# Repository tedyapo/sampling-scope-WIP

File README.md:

# sampling-scope-WIP
Work towards an open-source multi-GHz sampling oscilloscope design

Board designs are in Eagle. They are 4-layer, so require a subscription license to edit (I believe).

NB: as titled, this project is very much a work-in-progress. Completed designs will be published elsewhere.

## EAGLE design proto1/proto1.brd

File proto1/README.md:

# proto 1

This version does not include internal timebase calibration.

Initial testing has shown that it functions as a sampling oscilloscope with a bandwidth of approximately 6.7 GHz.

There is an error in this design: I swapped op-amps at the last minute, and accidentally reversed the inputs in the scheamtic. The board needs rework to correct this.

This version is abandoned, as it was never entended as a final product, just as a testbed for an evolving design.

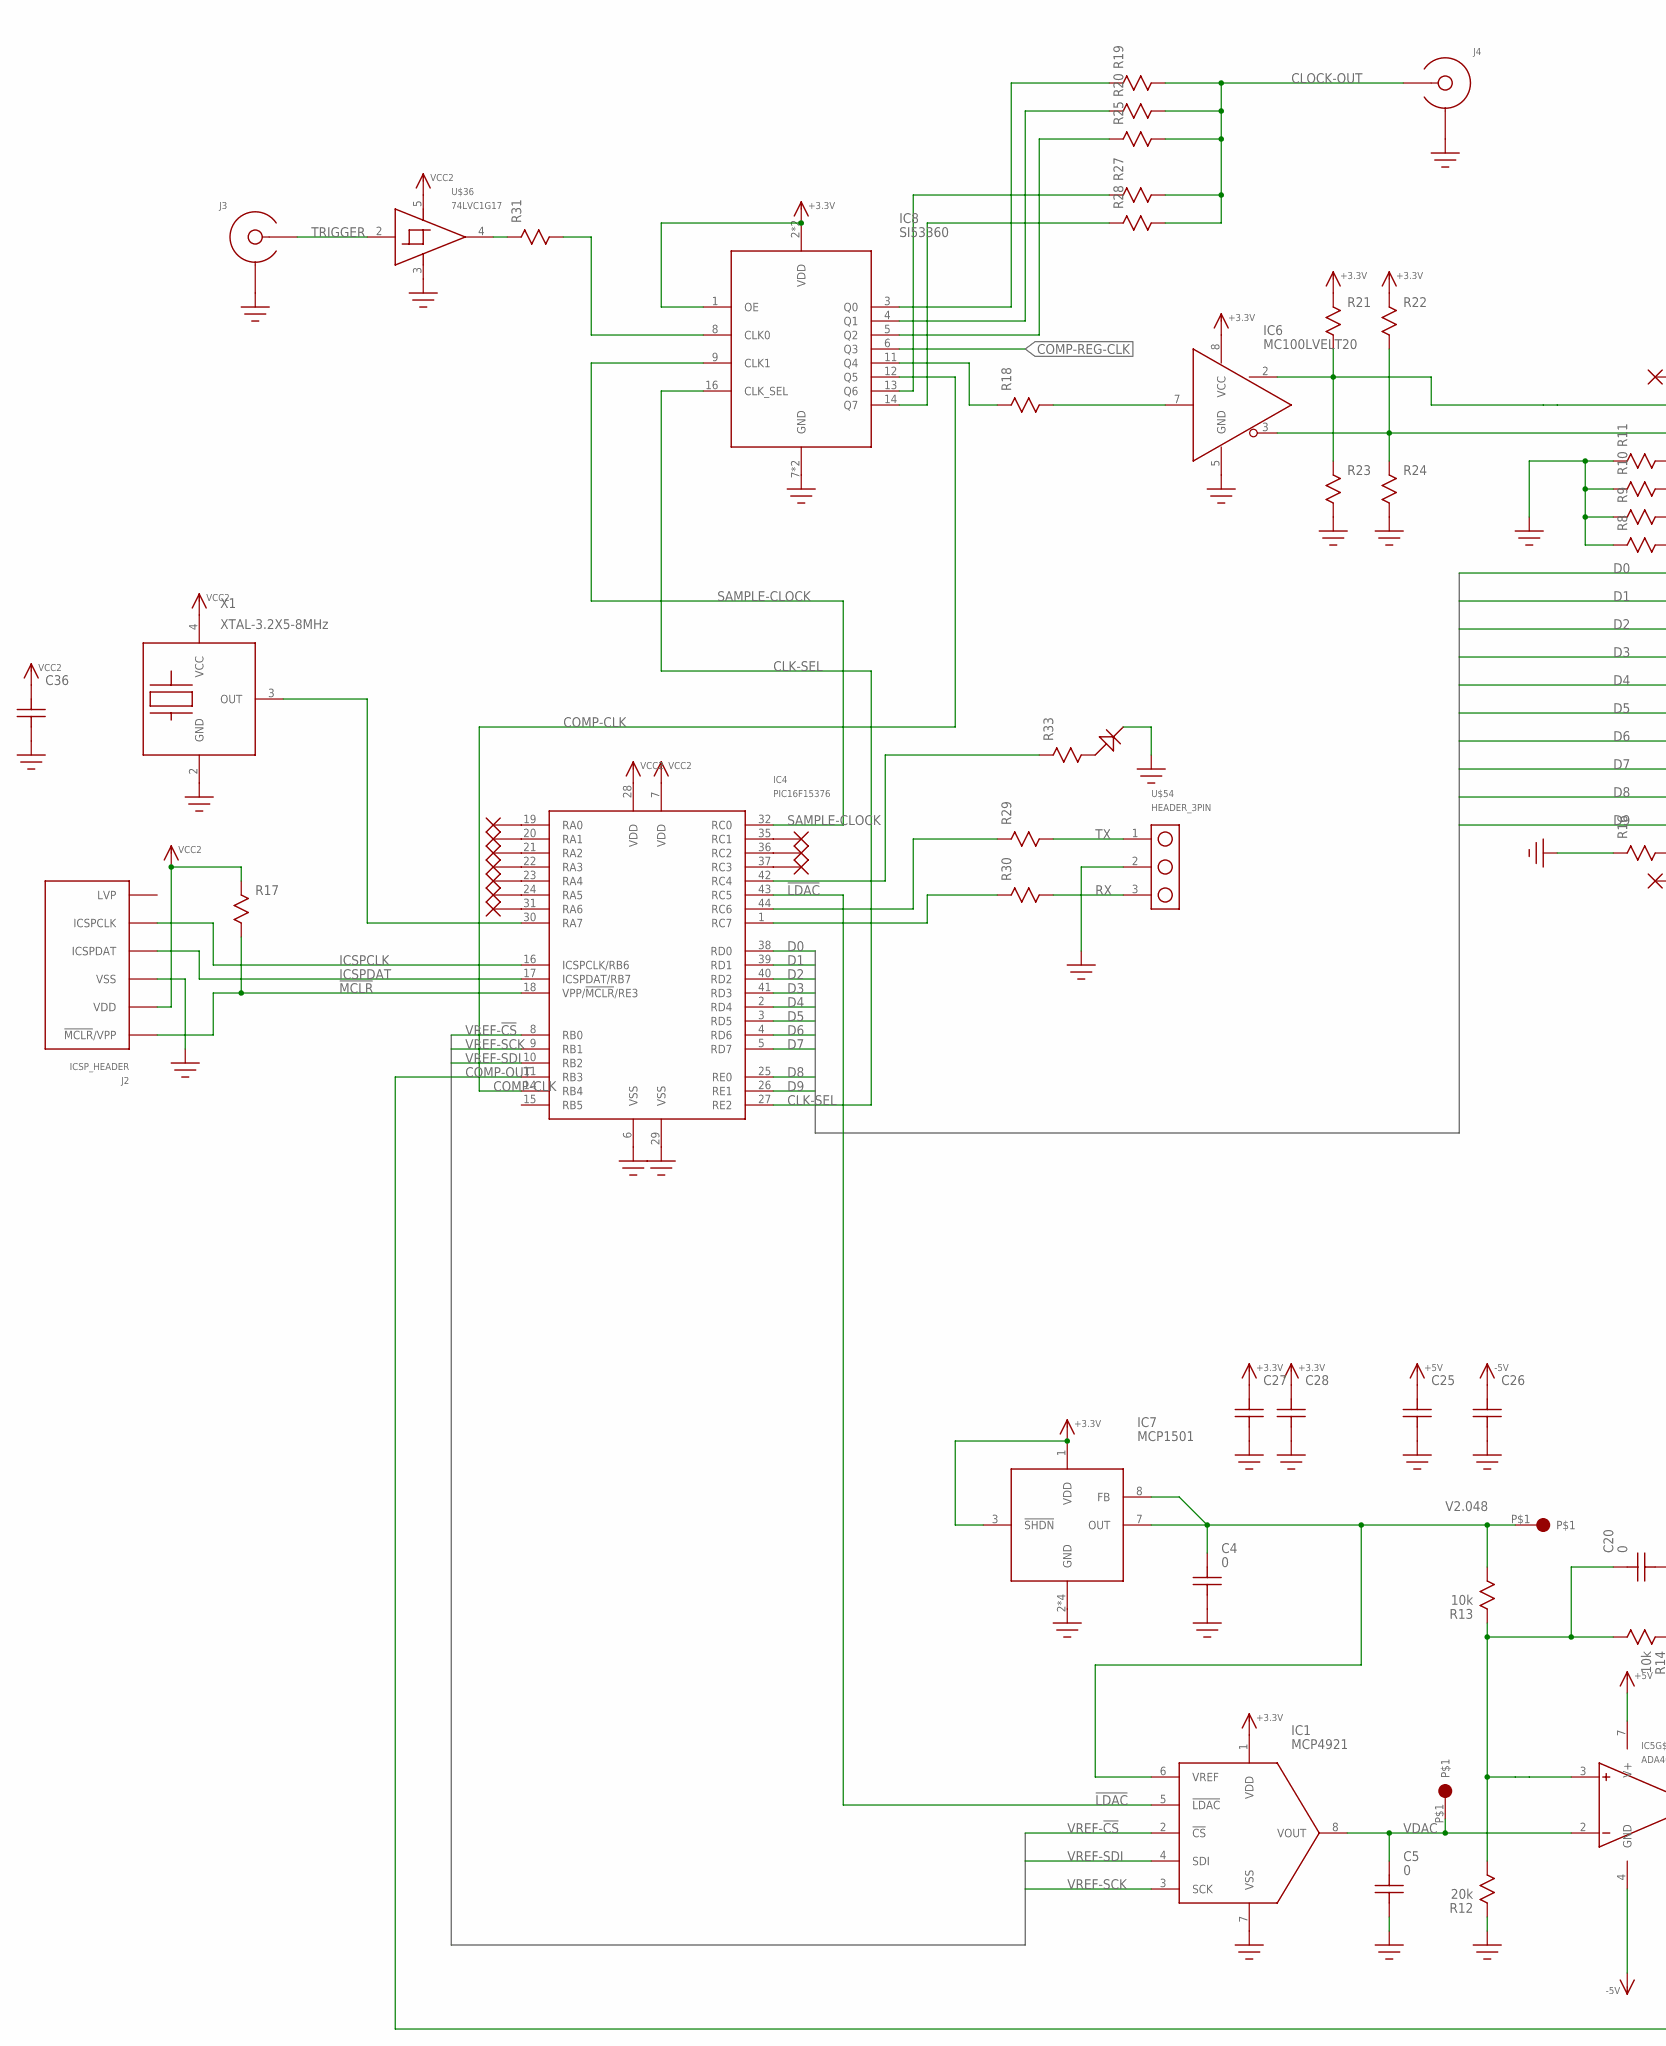
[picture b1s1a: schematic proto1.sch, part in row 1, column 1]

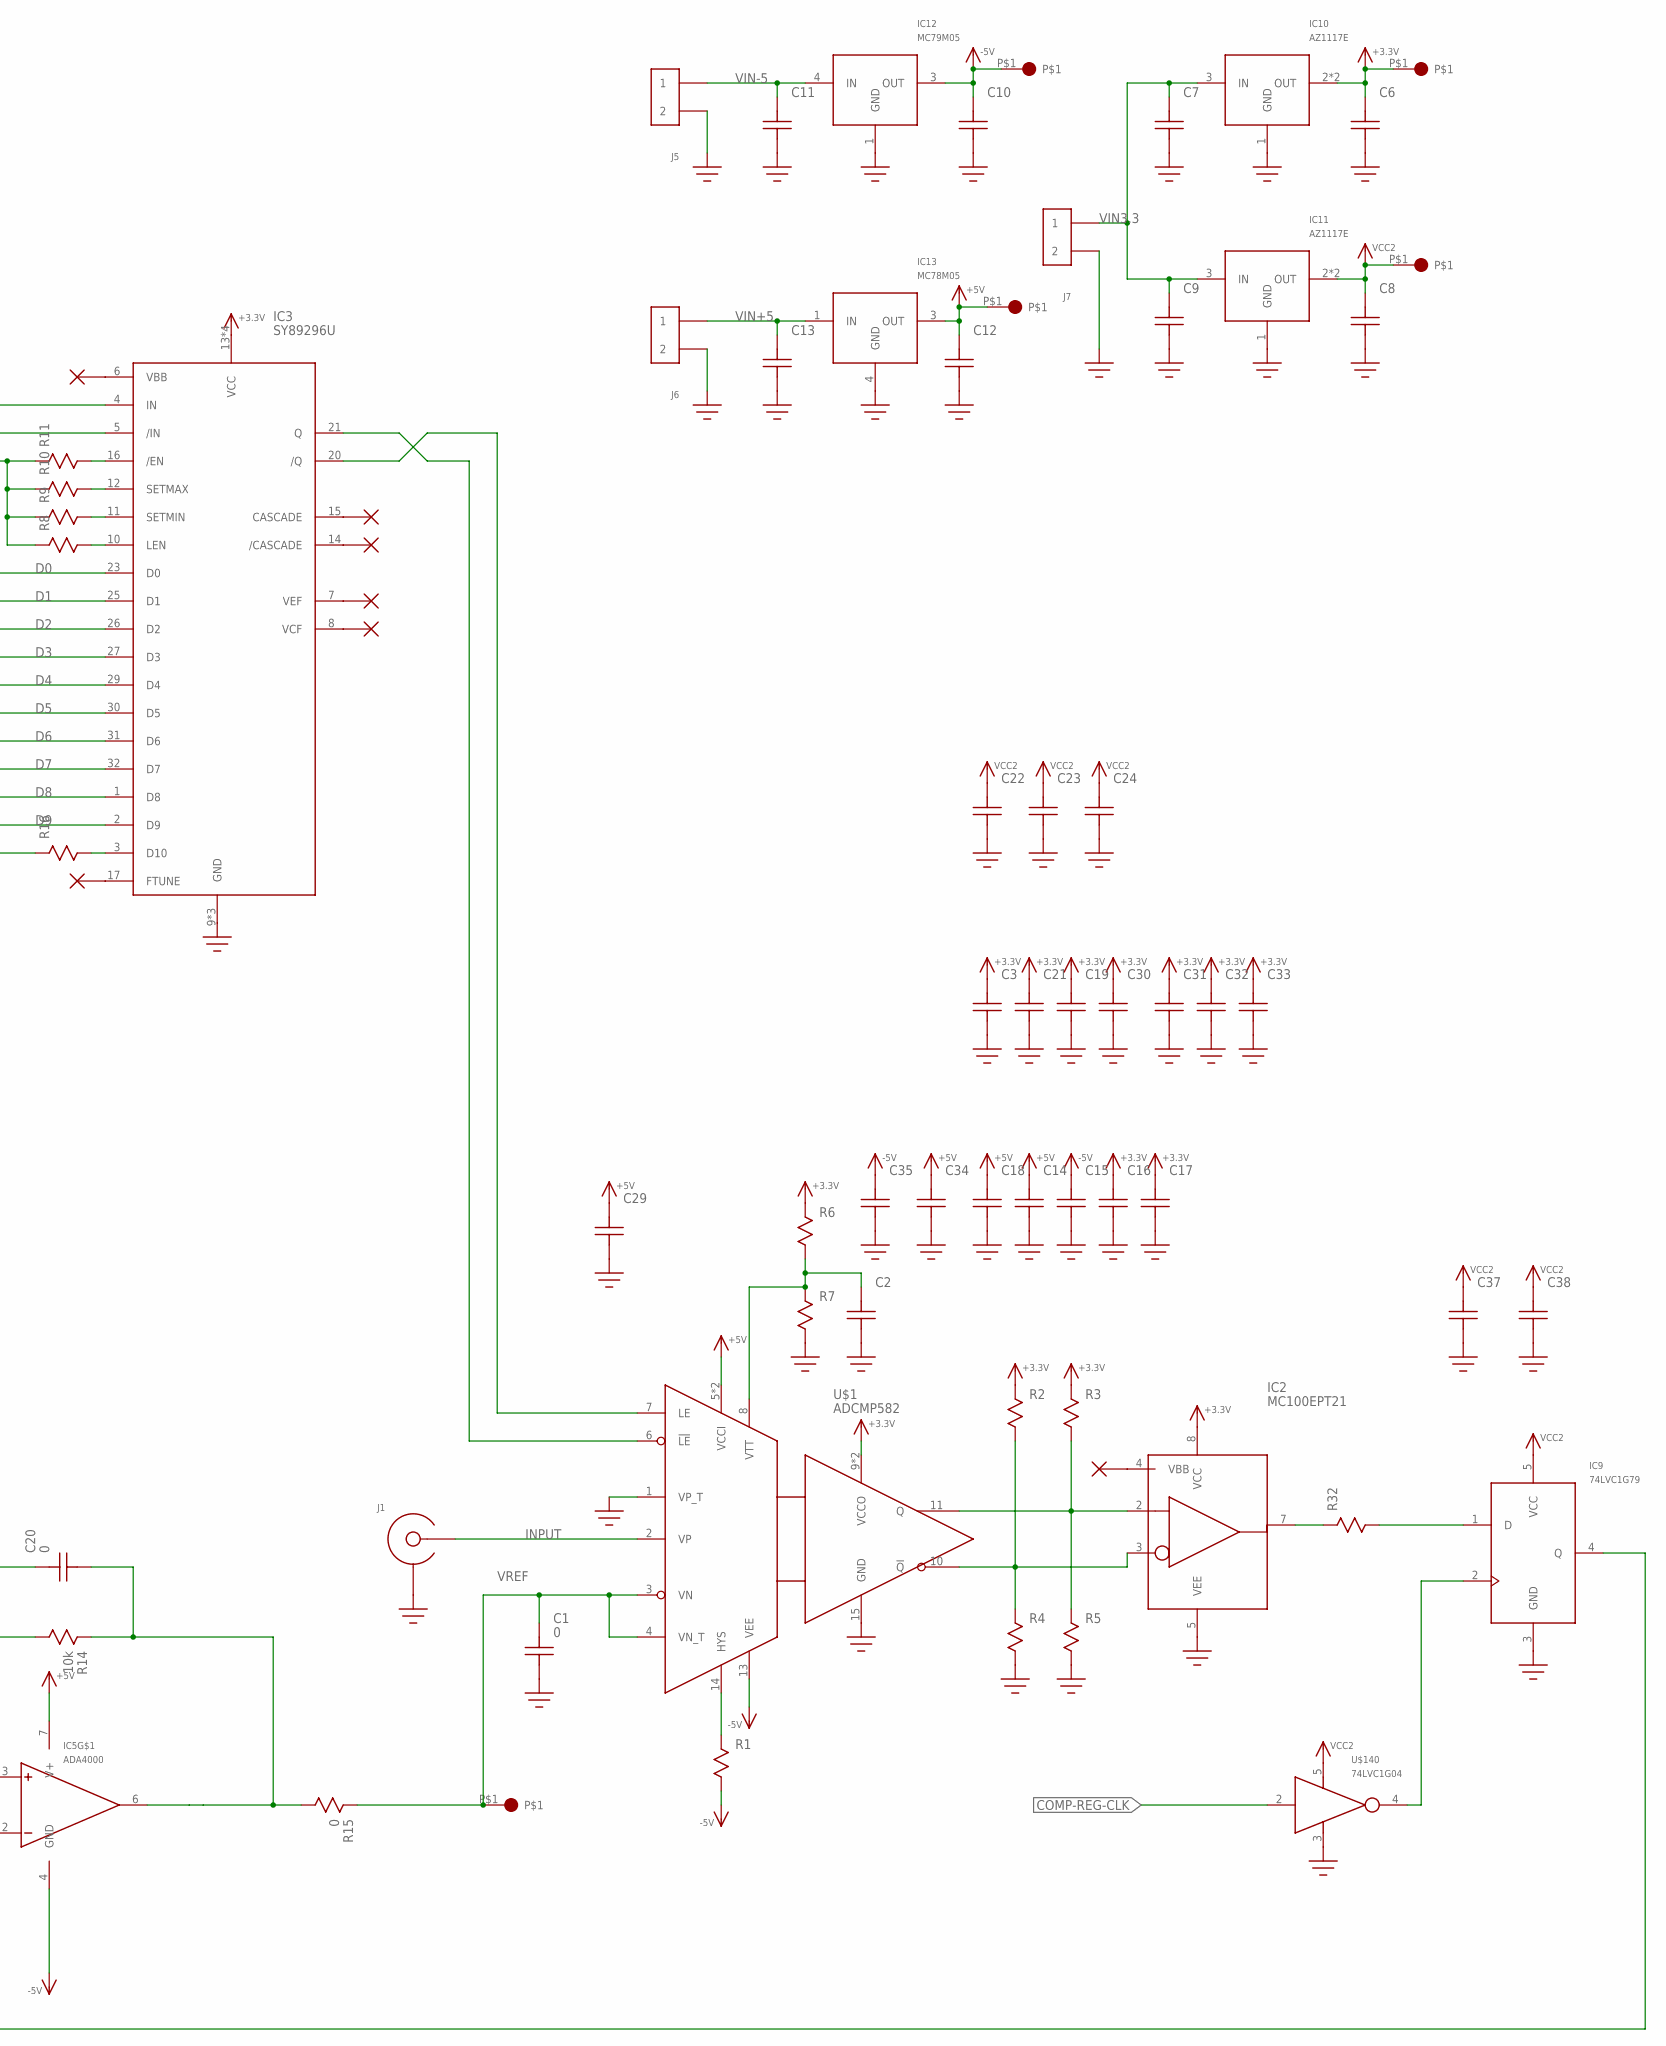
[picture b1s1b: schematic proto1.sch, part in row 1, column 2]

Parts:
C1, C4, C5, C20: 0; C0603
C2, C14, C15, C16, C17, C18: C0402_NO_THERMALS
C3, C19, C21, C22, C23, C24, C25, C26, C27, C28, C30, C31, C32, C33, C34, C35, C36, C37, C38: C0603
C6, C7, C8, C9, C10, C11, C12, C13, C29: C1206; 1206
IC1: MCP4921; SOIC8
IC2: MC100EPT21; SOIC8
IC3: SY89296U; TQFP32_7X7
IC4: PIC16F15376; TQFP44
IC5: ADA4000; SOIC8
IC6: MC100LVELT20; SOIC8
IC7: MCP1501; SOIC8
IC8: SI53360; TSSOP16
IC9: 74LVC1G79; SOT23-5
IC10, IC11: AZ1117E; SOT-223
IC12: MC79M05; DPAK
IC13: MC78M05; DPAK
J1, J3, J4: SMA-EDGE-LAUNCH4L-4020-TAPER-FIXED; SMA_EDGE_LAUNCH_4L_4020_TAPER_FIXED
J2: ICSP_HEADER; HEADER_6PIN
J5, J6, J7: HEADER_2PINSCREW-TERM; FCI_20020316_SCREW_TERM_2P
P1, P2, P3, P4, P5, P6, P7: ICSP_PAD
R1, R2, R3, R4, R5, R6, R7, R16, R17, R18, R21, R22, R23, R24, R29, R30, R31, R32, R33: R0603
R8, R9, R10, R11, R19, R20, R25, R27, R28: R0402; 0402
R12: 20k; R0603
R13, R14: 10k; R0603
R15: 0; R0603
U$1: ADCMP582; TQFN16-EP
U$36: 74LVC1G17; SOT23-5
U$54: HEADER_3PIN
U$88: LED_0603
U$140: 74LVC1G04; SOT23-5
X1: XTAL-3.2X5-8MHz; XTAL_3.2X5

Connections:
!LDAC!: IC1.5 (!LDAC!), IC4.43 (RC5)
!MCLR!: IC4.18 (VPP/!MCLR!/RE3), J2.1 (!MCLR!/VPP), R17.P$2
+3.3V: C3.P$2, C6.P$2, C16.2, C17.2, C19.P$2, C21.P$2, C27.P$2, C28.P$2, C30.P$2, C31.P$2, C32.P$2, C33.P$2, IC1.1 (VDD), IC2.8 (VCC), IC3.13 (VCC), IC3.18 (VCC), IC3.19 (VCC), IC3.22 (VCC), IC6.8 (VCC), IC7.1 (VDD), IC7.3 (!SHDN!), IC8.1 (OE), IC8.2 (VDD), IC8.15 (VDD), IC10.2 (OUT), IC10.4 (OUT), P5.P$1, R2.P$1, R3.P$1, R6.P$1, R21.P$1, R22.P$1, U$1.9 (VCCO), U$1.12 (VCCO)
+5V: C12.P$2, C14.2, C18.2, C25.P$2, C29.P$2, C34.P$2, IC5.7 (V+), IC13.3 (OUT), P4.P$1, U$1.5 (VCCI), U$1.16 (VCCI)
-5V: C10.P$2, C15.2, C26.P$2, C35.P$2, IC5.4 (GND), IC12.3 (OUT), P3.P$1, R1.P$2, U$1.13 (VEE)
CLK-SEL: IC4.27 (RE2), IC8.16 (CLK_SEL)
CLOCK-OUT: J4.CENTER@1 (CENTER), J4.P$3 (CENTER), R19.2, R20.2, R25.2, R27.2, R28.2
COMP-CLK: IC4.14 (RB4), IC8.12 (Q5)
COMP-OUT: IC4.11 (RB3), IC9.4 (Q)
COMP-REG-CLK: IC8.6 (Q3), U$140.2 (IN)
D0: IC3.23 (D0), IC4.38 (RD0)
D1: IC3.25 (D1), IC4.39 (RD1)
D2: IC3.26 (D2), IC4.40 (RD2)
D3: IC3.27 (D3), IC4.41 (RD3)
D4: IC3.29 (D4), IC4.2 (RD4)
D5: IC3.30 (D5), IC4.3 (RD5)
D6: IC3.31 (D6), IC4.4 (RD6)
D7: IC3.32 (D7), IC4.5 (RD7)
D8: IC3.1 (D8), IC4.25 (RE0)
D9: IC3.2 (D9), IC4.26 (RE1)
GND: C1.P$1, C2.1, C3.P$1, C4.P$1, C5.P$1, C6.P$1, C7.P$1, C8.P$1, C9.P$1, C10.P$1, C11.P$1, C12.P$1, C13.P$1, C14.1, C15.1, C16.1, C17.1, C18.1, C19.P$1, C21.P$1, C22.P$1, C23.P$1, C24.P$1, C25.P$1, C26.P$1, C27.P$1, C28.P$1, C29.P$1, C30.P$1, C31.P$1, C32.P$1, C33.P$1, C34.P$1, C35.P$1, C36.P$1, C37.P$1, C38.P$1, IC1.7 (VSS), IC2.5 (VEE), IC3.9 (GND), IC3.24 (GND), IC3.28 (GND), IC4.6 (VSS), IC4.29 (VSS), IC6.5 (GND), IC7.2 (GND), IC7.4 (GND), IC7.5 (GND), IC7.6 (GND), IC8.7 (GND), IC8.10 (GND), IC9.3 (GND), IC10.1 (GND), IC11.1 (GND), IC12.1 (GND), IC13.4 (GND), J1.BOTTOM_GND (SHIELD), J1.GND@1 (SHIELD), J1.GND@2 (SHIELD), J1.GND@3 (SHIELD), J1.GND@4 (SHIELD), J1.GND@5 (SHIELD), J1.GND@6 (SHIELD), J1.GND@7 (SHIELD), J1.GND@8 (SHIELD), J1.GND@14 (SHIELD), J1.GND@15 (SHIELD), J1.GND@16 (SHIELD), J1.GND@17 (SHIELD), J1.GND_PAD1 (SHIELD), J1.GND_PAD2 (SHIELD), J1.P$1 (SHIELD), J1.P$2 (SHIELD), J2.3 (VSS), J3.BOTTOM_GND (SHIELD), J3.GND@1 (SHIELD), J3.GND@2 (SHIELD), J3.GND@3 (SHIELD), J3.GND@4 (SHIELD), J3.GND@5 (SHIELD), J3.GND@6 (SHIELD), J3.GND@7 (SHIELD), J3.GND@8 (SHIELD), J3.GND@14 (SHIELD), J3.GND@15 (SHIELD), J3.GND@16 (SHIELD), J3.GND@17 (SHIELD), J3.GND_PAD1 (SHIELD), J3.GND_PAD2 (SHIELD), J3.P$1 (SHIELD), J3.P$2 (SHIELD), J4.BOTTOM_GND (SHIELD), J4.GND@1 (SHIELD), J4.GND@2 (SHIELD), J4.GND@3 (SHIELD), J4.GND@4 (SHIELD), J4.GND@5 (SHIELD), J4.GND@6 (SHIELD), J4.GND@7 (SHIELD), J4.GND@8 (SHIELD), J4.GND@14 (SHIELD), J4.GND@15 (SHIELD), J4.GND@16 (SHIELD), J4.GND@17 (SHIELD), J4.GND_PAD1 (SHIELD), J4.GND_PAD2 (SHIELD), J4.P$1 (SHIELD), J4.P$2 (SHIELD), J5.P$2 (2), J6.P$2 (2), J7.P$2 (2), R4.P$2, R5.P$2, R7.P$2, R8.1, R9.1, R10.1, R11.1, R12.P$1, R16.P$1, R23.P$2, R24.P$2, U$1.1 (VP_T), U$1.15 (GND), U$36.3 (GND), U$54.2, U$88.C, U$140.3 (GND), X1.2 (GND)
ICSPCLK: IC4.16 (ICSPCLK/RB6), J2.5 (ICSPCLK)
ICSPDAT: IC4.17 (ICSPDAT/RB7), J2.4 (ICSPDAT)
INPUT: J1.CENTER@1 (CENTER), J1.P$3 (CENTER), U$1.2 (VP)
LE_N: IC3.21 (Q), U$1.6 (!LE!)
LE_P1: IC3.20 (/Q), U$1.7 (LE)
unnamed: R31.P$1, U$36.4 (OUT)
unnamed: R1.P$1, U$1.14 (HYS)
unnamed: IC2.2 (D), R3.P$2, R5.P$1, U$1.11 (Q)
unnamed: IC2.3 (!D!), R2.P$2, R4.P$1, U$1.10 (!Q!)
unnamed: C2.2, R6.P$2, R7.P$1, U$1.8 (VTT)
unnamed: IC3.16 (/EN), R11.2
unnamed: IC3.12 (SETMAX), R10.2
unnamed: IC3.11 (SETMIN), R9.2
unnamed: IC3.10 (LEN), R8.2
unnamed: IC3.4 (IN), IC6.2 (Q), R21.P$2, R23.P$1
unnamed: IC2.7 (Q), R32.P$1
unnamed: IC8.11 (Q4), R18.P$1
unnamed: IC9.2 (CLK), U$140.4 (OUT)
unnamed: C20.P$2, IC5.3 (+), R12.P$2, R13.P$1, R14.P$2
unnamed: C20.P$1, IC5.6 (OUT), R14.P$1, R15.P$2
unnamed: IC3.5 (/IN), IC6.3 (!Q!), R22.P$2, R24.P$1
unnamed: IC8.8 (CLK0), R31.P$2
unnamed: IC4.30 (RA7), X1.3 (OUT)
unnamed: IC4.42 (RC4), R33.P$1
unnamed: R33.P$2, U$88.A
unnamed: IC9.1 (D), R32.P$2
unnamed: IC3.3 (D10), R16.P$2
unnamed: IC6.7 (D), R18.P$2
unnamed: IC8.14 (Q7), R28.1
unnamed: IC8.13 (Q6), R27.1
unnamed: IC8.5 (Q2), R25.1
unnamed: IC8.4 (Q1), R20.1
unnamed: IC8.3 (Q0), R19.1
unnamed: IC4.44 (RC6), R29.P$1
unnamed: IC4.1 (RC7), R30.P$1
RX: R30.P$2, U$54.3
SAMPLE-CLOCK: IC4.32 (RC0), IC8.9 (CLK1)
TRIGGER: J3.CENTER@1 (CENTER), J3.P$3 (CENTER), U$36.2 (IN)
TX: R29.P$2, U$54.1
V2.048: C4.P$2, IC1.6 (VREF), IC7.7 (OUT), IC7.8 (FB), P7.P$1, R13.P$2
VCC2: C8.P$2, C22.P$2, C23.P$2, C24.P$2, C36.P$2, C37.P$2, C38.P$2, IC4.7 (VDD), IC4.28 (VDD), IC9.5 (VCC), IC11.2 (OUT), IC11.4 (OUT), J2.2 (VDD), P6.P$1, R17.P$1, U$36.5 (VCC), U$140.5 (VCC), X1.4 (VCC)
VDAC: C5.P$2, IC1.8 (VOUT), IC5.2 (-), P2.P$1
VIN3.3: C7.P$2, C9.P$2, IC10.3 (IN), IC11.3 (IN), J7.P$1 (1)
VIN+5: C13.P$2, IC13.1 (IN), J6.P$1 (1)
VIN-5: C11.P$2, IC12.4 (IN), J5.P$1 (1)
VREF: C1.P$2, P1.P$1, R15.P$1, U$1.3 (VN), U$1.4 (VN_T)
VREF-!CS!: IC1.2 (!CS!), IC4.8 (RB0)
VREF-SCK: IC1.3 (SCK), IC4.9 (RB1)
VREF-SDI: IC1.4 (SDI), IC4.10 (RB2)

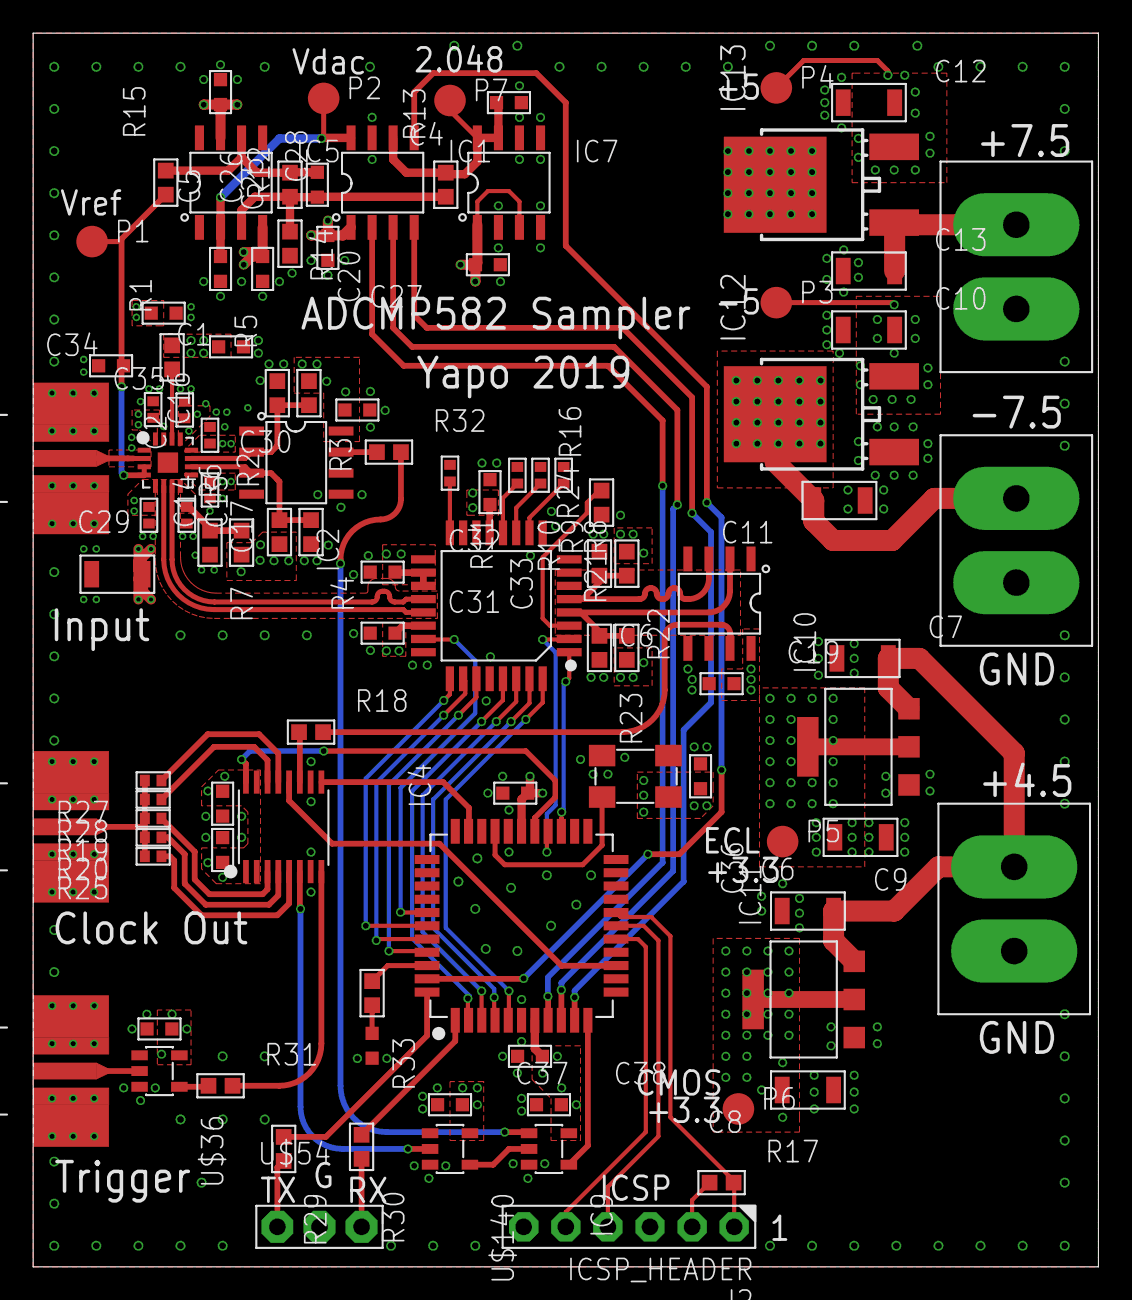
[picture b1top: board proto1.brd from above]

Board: 4 copper layers, 64.3 x 74.4 mm, 103 parts (0 on the bottom side), 70 nets.

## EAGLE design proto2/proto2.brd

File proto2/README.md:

# proto2

This version incorporates the timebase calibration loop.

It has not been fully tested yet.

This version will be abandoned, as it was never entended as a final product, just as a testbed for an evolving design.

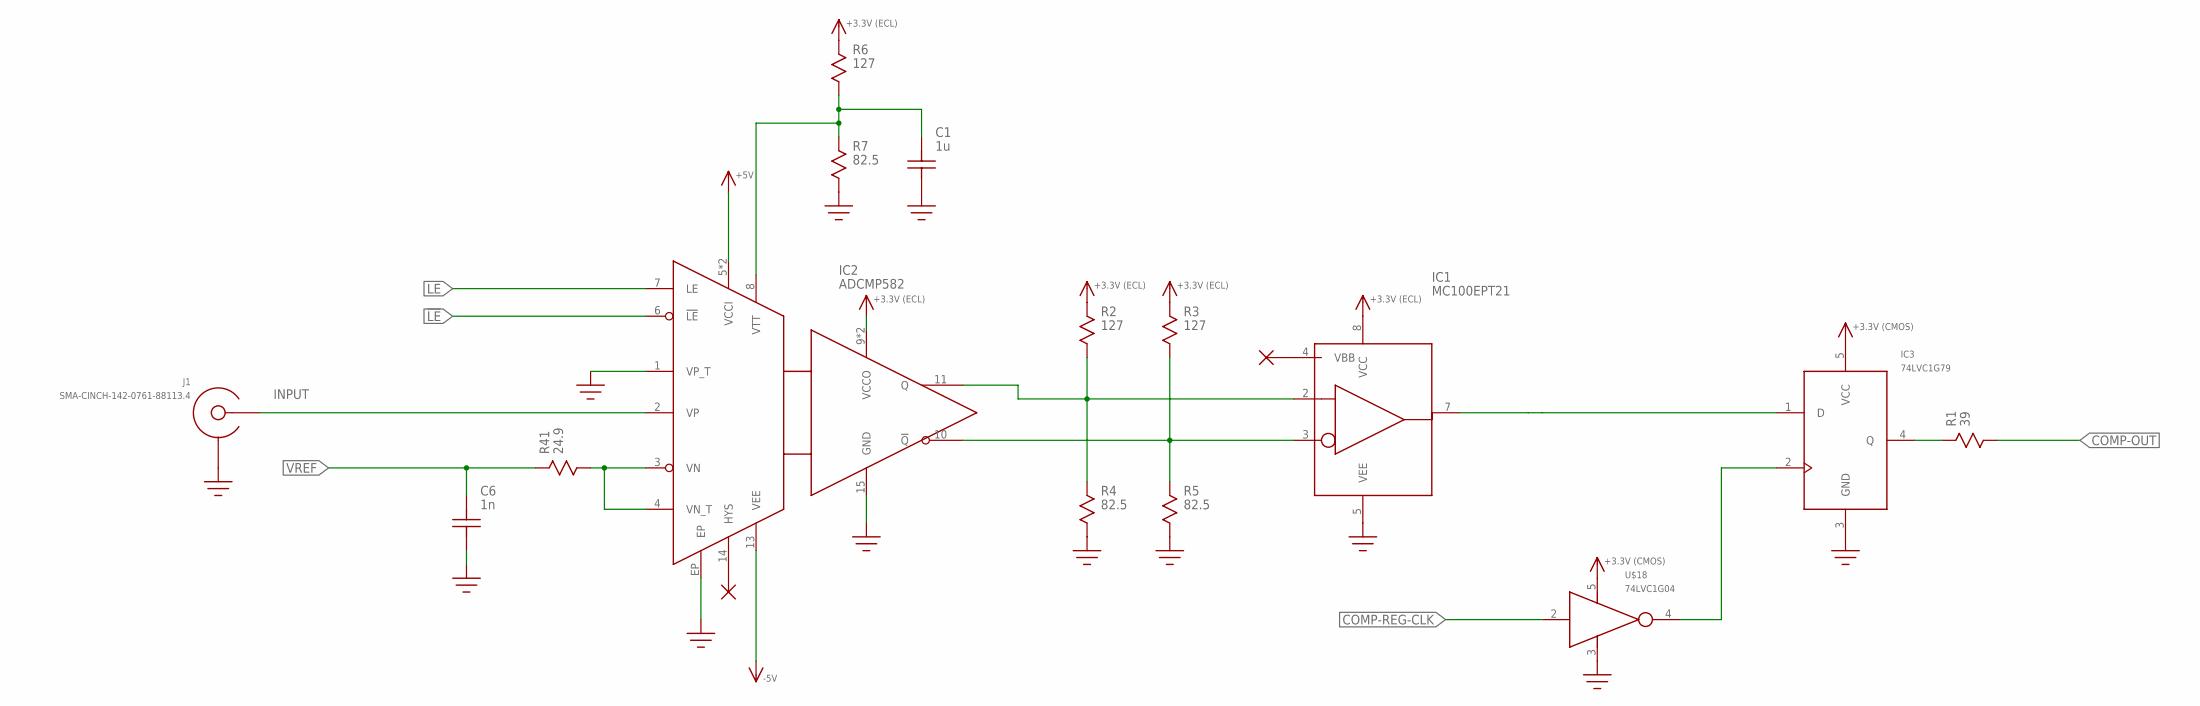
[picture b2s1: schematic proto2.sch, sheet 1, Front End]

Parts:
C1: 1u; C0402
C6: 1n; C0402
IC1: MC100EPT21; SOIC8
IC2: ADCMP582; TQFN16-EP
IC3: 74LVC1G79; SOT23-5
J1: SMA-CINCH-142-0761-88113.4; SMA-CINCH-142-0761-881-13.4
R1: 39; R0603
R2, R3, R6: 127; R0603
R4, R5, R7: 82.5; R0603
R41: 24.9; 0402
U$18: 74LVC1G04; SOT23-5

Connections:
!LE!: IC2.6 (!LE!); also elsewhere on the board
+5V: IC2.5 (VCCI), IC2.16 (VCCI); also elsewhere on the board
-5V: IC2.13 (VEE); also elsewhere on the board
COMP-OUT: R1.P$2; also elsewhere on the board
COMP-REG-CLK: U$18.2 (IN); also elsewhere on the board
GND: C1.1, C6.1, IC1.5 (VEE), IC2.1 (VP_T), IC2.15 (GND), IC2.EP, IC3.3 (GND), J1.GND@1 (SHIELD), J1.GND@2 (SHIELD), J1.GND@3 (SHIELD), J1.HOLE@1 (SHIELD), J1.HOLE@2 (SHIELD), J1.HOLE@3 (SHIELD), J1.HOLE@4 (SHIELD), J1.VIA@1 (SHIELD), J1.VIA@2 (SHIELD), J1.VIA@3 (SHIELD), J1.VIA@4 (SHIELD), J1.VIA@5 (SHIELD), J1.VIA@6 (SHIELD), R4.P$2, R5.P$2, R7.P$2, U$18.3 (GND); also elsewhere on the board
INPUT: IC2.2 (VP), J1.CENTER
LE: IC2.7 (LE); also elsewhere on the board
unnamed: C1.2, IC2.8 (VTT), R6.P$2, R7.P$1
unnamed: IC1.3 (!D!), IC2.10 (!Q!), R3.P$2, R5.P$1
unnamed: IC1.2 (D), IC2.11 (Q), R2.P$2, R4.P$1
unnamed: IC1.7 (Q), IC3.1 (D)
unnamed: IC3.4 (Q), R1.P$1
unnamed: IC3.2 (CLK), U$18.4 (OUT)
unnamed: IC2.3 (VN), IC2.4 (VN_T), R41.2
VCC1: IC1.8 (VCC), IC2.9 (VCCO), IC2.12 (VCCO), R2.P$1, R3.P$1, R6.P$1; also elsewhere on the board
VCC2: IC3.5 (VCC), U$18.5 (VCC); also elsewhere on the board
VREF: C6.2, R41.1; also elsewhere on the board

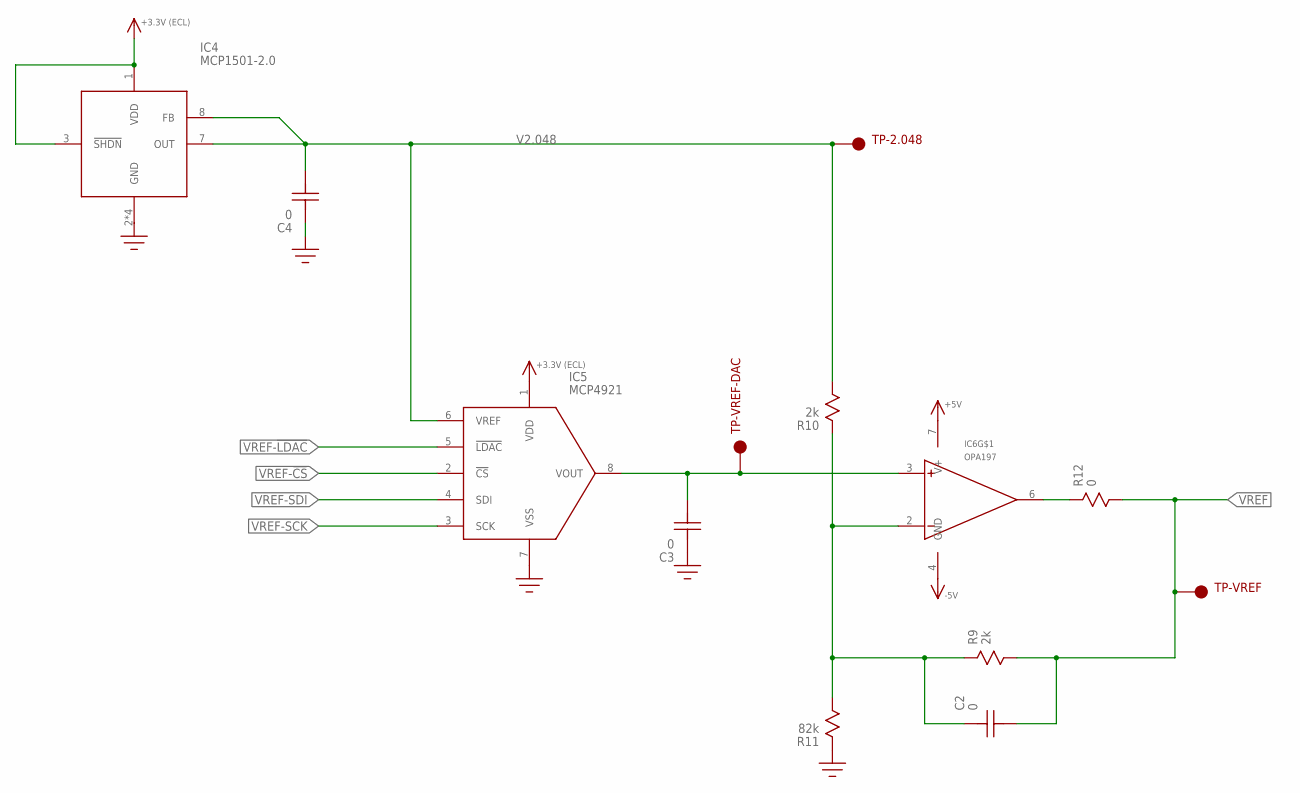
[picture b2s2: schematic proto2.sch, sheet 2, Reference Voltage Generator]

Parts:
C2, C3, C4: 0; C0603
IC4: MCP1501-2.0; SOIC8
IC5: MCP4921; SOIC8
IC6: OPA197; SOIC8
R9, R10: 2k; R0603
R11: 82k; R0603
R12: 0; R0603
TP-2.048: ICSP_PAD
TP-VREF: ICSP_PAD
TP-VREF-DAC: ICSP_PAD

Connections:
+5V: IC6.7 (V+); also elsewhere on the board
-5V: IC6.4 (GND); also elsewhere on the board
GND: C3.P$2, C4.P$2, IC4.2 (GND), IC4.4 (GND), IC4.5 (GND), IC4.6 (GND), IC5.7 (VSS), R11.P$1; also elsewhere on the board
unnamed: C2.P$2, IC6.2 (-), R9.P$1, R10.P$1, R11.P$2
unnamed: IC6.6 (OUT), R12.P$1
unnamed: C3.P$1, IC5.8 (VOUT), IC6.3 (+), TP-VREF-DAC.P$1
V2.048: C4.P$1, IC4.7 (OUT), IC4.8 (FB), IC5.6 (VREF), R10.P$2, TP-2.048.P$1
VCC1: IC4.1 (VDD), IC4.3 (!SHDN!), IC5.1 (VDD); also elsewhere on the board
VREF: C2.P$1, R9.P$2, R12.P$2, TP-VREF.P$1; also elsewhere on the board
VREF-!CS!: IC5.2 (!CS!); also elsewhere on the board
VREF-!LDAC!: IC5.5 (!LDAC!); also elsewhere on the board
VREF-SCK: IC5.3 (SCK); also elsewhere on the board
VREF-SDI: IC5.4 (SDI); also elsewhere on the board

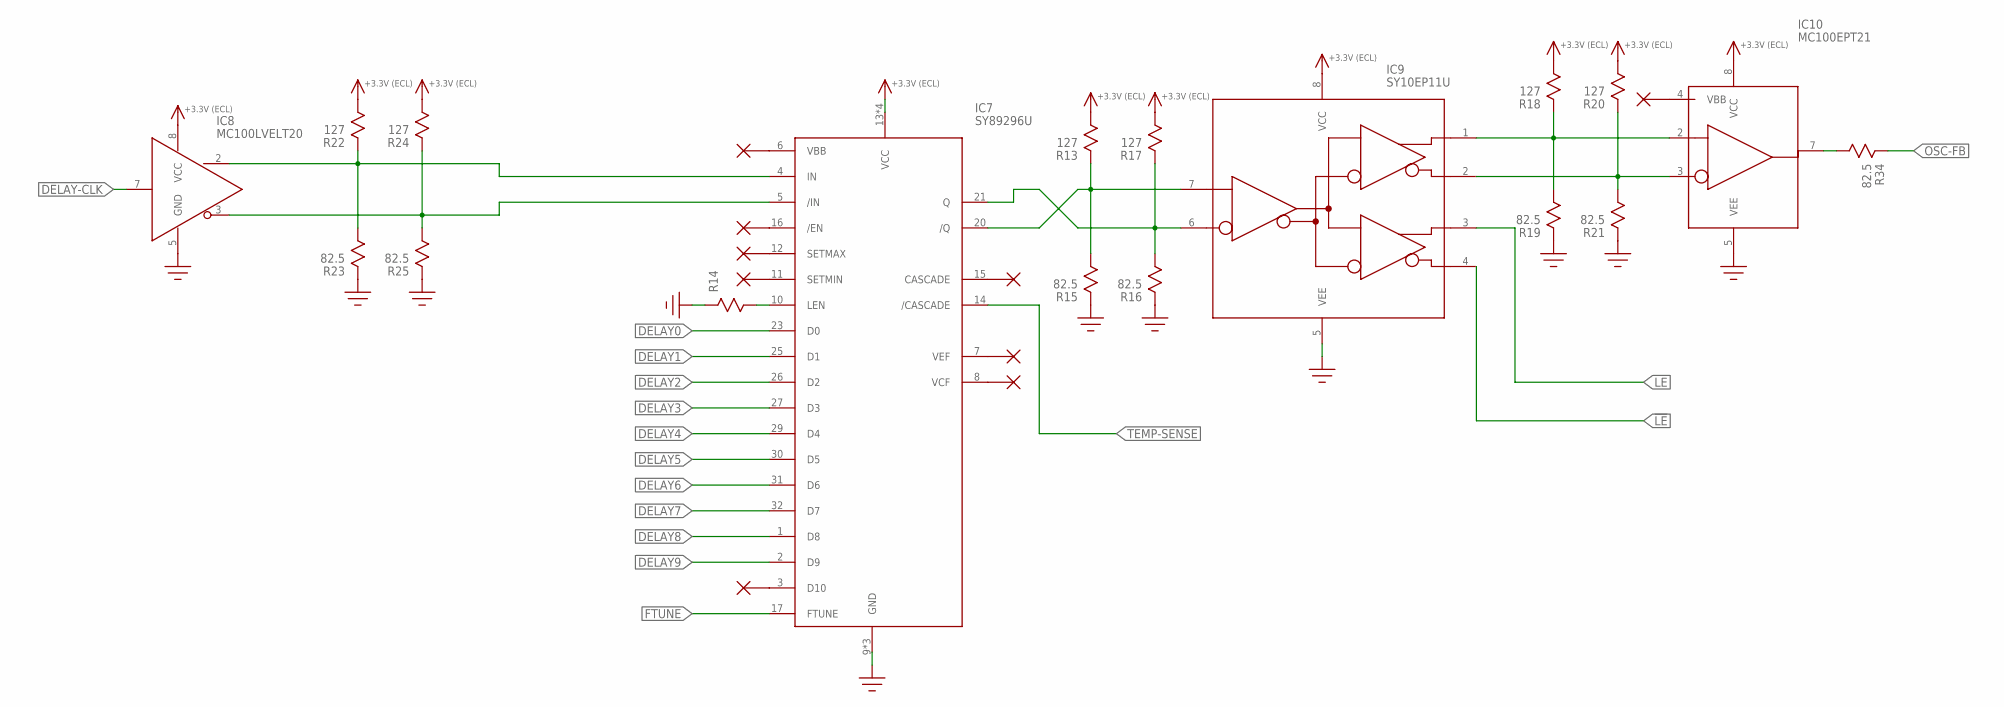
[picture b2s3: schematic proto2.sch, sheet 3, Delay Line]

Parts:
IC7: SY89296U; TQFP32_7X7
IC8: MC100LVELT20; SOIC8
IC9: SY10EP11U; SOIC8
IC10: MC100EPT21; SOIC8
R13, R17, R18, R20, R22, R24: 127; R0603
R14: R0603
R15, R16, R19, R21, R23, R25, R34: 82.5; R0603

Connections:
!LE!: IC9.4 (!Q1!); also elsewhere on the board
DELAY0: IC7.23 (D0); also elsewhere on the board
DELAY1: IC7.25 (D1); also elsewhere on the board
DELAY2: IC7.26 (D2); also elsewhere on the board
DELAY3: IC7.27 (D3); also elsewhere on the board
DELAY4: IC7.29 (D4); also elsewhere on the board
DELAY5: IC7.30 (D5); also elsewhere on the board
DELAY6: IC7.31 (D6); also elsewhere on the board
DELAY7: IC7.32 (D7); also elsewhere on the board
DELAY8: IC7.1 (D8); also elsewhere on the board
DELAY9: IC7.2 (D9); also elsewhere on the board
DELAY-!IN!: IC7.5 (/IN), IC8.3 (!Q!), R24.P$1, R25.P$2
DELAY-CLK: IC8.7 (D); also elsewhere on the board
DELAY-IN: IC7.4 (IN), IC8.2 (Q), R22.P$1, R23.P$2
FTUNE: IC7.17 (FTUNE); also elsewhere on the board
GND: IC7.9 (GND), IC7.24 (GND), IC7.28 (GND), IC8.5 (GND), IC9.5 (VEE), IC10.5 (VEE), R14.P$1, R15.P$1, R16.P$1, R19.P$1, R21.P$1, R23.P$1, R25.P$1; also elsewhere on the board
LE: IC9.3 (Q1); also elsewhere on the board
unnamed: IC7.10 (LEN), R14.P$2
unnamed: IC10.7 (Q), R34.P$2
unnamed: IC7.20 (/Q), IC9.7 (D), R13.P$1, R15.P$2
unnamed: IC9.1 (Q0), IC10.2 (D), R18.P$1, R19.P$2
unnamed: IC7.21 (Q), IC9.6 (!D!), R16.P$2, R17.P$1
unnamed: IC9.2 (!Q0!), IC10.3 (!D!), R20.P$1, R21.P$2
OSC-FB: R34.P$1; also elsewhere on the board
TEMP-SENSE: IC7.14 (/CASCADE); also elsewhere on the board
VCC1: IC7.13 (VCC), IC7.18 (VCC), IC7.19 (VCC), IC7.22 (VCC), IC8.8 (VCC), IC9.8 (VCC), IC10.8 (VCC), R13.P$2, R17.P$2, R18.P$2, R20.P$2, R22.P$2, R24.P$2; also elsewhere on the board

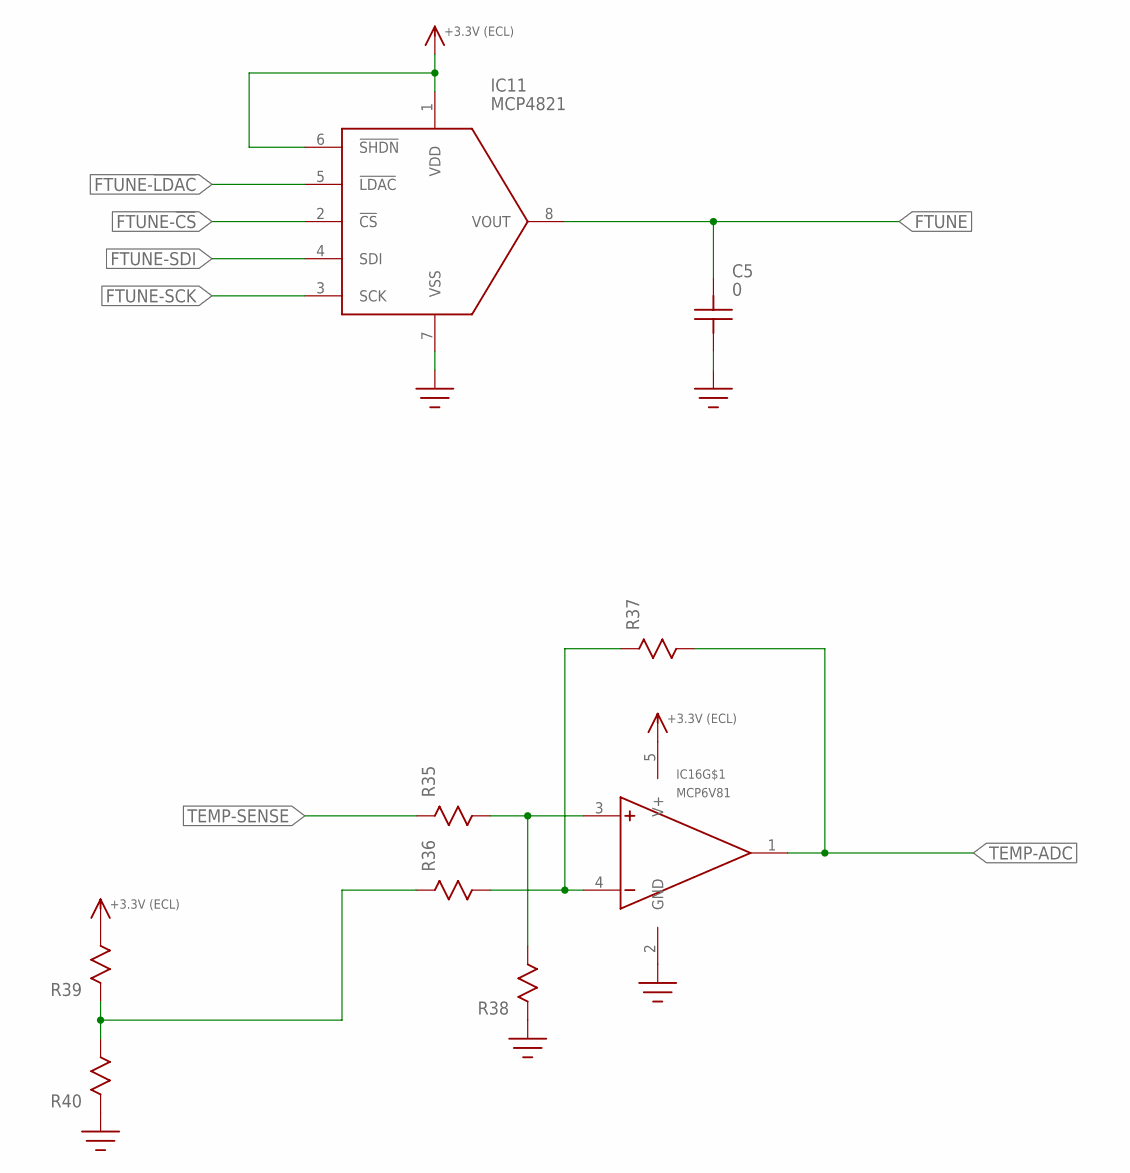
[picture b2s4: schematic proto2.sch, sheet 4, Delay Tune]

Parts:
C5: 0; C0603
IC11: MCP4821; SOIC8
IC16: MCP6V81; SOT23-5
R35, R36, R37, R38, R39, R40: R0603

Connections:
FTUNE: C5.P$2, IC11.8 (VOUT); also elsewhere on the board
FTUNE-!CS!: IC11.2 (!CS!); also elsewhere on the board
FTUNE-!LDAC!: IC11.5 (!LDAC!); also elsewhere on the board
FTUNE-SCK: IC11.3 (SCK); also elsewhere on the board
FTUNE-SDI: IC11.4 (SDI); also elsewhere on the board
GND: C5.P$1, IC11.7 (VSS), IC16.2 (GND), R38.P$1, R40.P$1; also elsewhere on the board
unnamed: IC16.3 (+), R35.P$2, R38.P$2
unnamed: IC16.4 (-), R36.P$2, R37.P$1
unnamed: R36.P$1, R39.P$1, R40.P$2
TEMP-ADC: IC16.1 (OUT), R37.P$2; also elsewhere on the board
TEMP-SENSE: R35.P$1; also elsewhere on the board
VCC1: IC11.1 (VDD), IC11.6 (!SHDN!), IC16.5 (V+), R39.P$2; also elsewhere on the board
